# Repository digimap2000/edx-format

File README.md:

# EDX, the Electronics Design eXchange

EDX is an open, tool-neutral file format for printed circuit board design data. The design side states what the
board is and what it must achieve: outline, stack-up, packages, parts, nets, regions, pours, design-intent
relations, rules and explicit constraints. A layout engine decides how, and returns placement, copper and a report
in the same terms.

An EDX document is one JSON file (`*.edx.json`) with optional sections: `design`, `rules`, `constraints`, and the
engine's `layout` and `report`. Documents holding different sections, such as a design and a set of rules, merge into
one. Areas are written as SVG path data.

**Status:** pre-release. The specification, [`spec/edx.md`](spec/edx.md), is a working draft of version 1.0; nothing is stable yet.

## What lives here

| Folder | Contents |
| --- | --- |
| `spec/` | The specification, the normative definition of EDX |
| `schema/` | The JSON Schema (2020-12) for an EDX document, normative alongside the spec |
| `conformance/` | Language-neutral test cases and example documents |
| `crates/edx-format/` | Reference library in Rust: check, read, merge and write EDX documents |
| `crates/edx-cli/` | `edx`, the command-line checker and merger |
| `crates/edx-kicad/` | Converts KiCad 6+ boards to EDX (`edx from-kicad`), with no KiCad running |
| `bindings/python/` | The Python package `edx-format`, built on the Rust library |
| `bindings/js/` | The JavaScript package `edx-format`, the Rust library compiled to WebAssembly |
| `site/` | The GitHub Pages site that serves the schema at its `$id` |
| `tools/` | Scripts that check the suite against the schema and run it against any implementation |

## The reference library

The Rust crate `edx-format` checks a document in the four layers of the specification (parse, version and
extensions, schema, semantics), reads it into a typed model that keeps every `extensions` and `extras` member, merges
documents by record identity, and writes them back, plainly or in canonical form, with the section hashes a layout
engine records.

```rust
let checked = edx_format::check(&std::fs::read("board.edx.json")?);
for diagnostic in &checked.diagnostics {
    println!("{diagnostic}"); // error EDX-E2001: /design/parts/3/package: no package `SOT23`
}
if let Some(document) = checked.document.filter(|_| checked.is_ok()) {
    println!("{} parts", document.design.and_then(|d| d.parts).map_or(0, |p| p.len()));
}
```

The `edx` command does the same from a shell:

```sh
cargo install --path crates/edx-cli
edx check board.edx.json                 # exit status 1 when the document has errors
edx check --format json board.edx.json   # diagnostics as JSON, for other tools
edx merge design.edx.json rules.edx.json -o merged.edx.json
edx fmt board.edx.json                   # canonical form (section 13 of the spec)
edx hash board.edx.json                  # sha256 of the design, rules and constraints
edx constraints board.edx.json           # the constraints in force, derived and authored
edx explain EDX-E3005
edx from-kicad board.kicad_pcb -o board.edx.json   # a KiCad 6+ board as EDX
```

Converting from KiCad is one of the free utilities offered beside the specification; see
[`crates/edx-kicad`](crates/edx-kicad/README.md) for what goes where.

To depend on it from another Rust project before it is on crates.io:

```toml
edx-format = { git = "https://github.com/digimap2000/edx-format" }
```

## Python and JavaScript

Both packages wrap the same Rust core, so their results match it exactly, and both install the same `edx` command.
Documents are plain dictionaries or objects. See [`bindings/python`](bindings/python/README.md) and
[`bindings/js`](bindings/js/README.md).

```sh
pip install ./bindings/python                      # needs a Rust toolchain; builds with maturin
cd bindings/js && npm run build && npm test        # needs the wasm32 target and wasm-bindgen-cli
```

## Running the conformance suite

```sh
cargo test                                         # the reference library, including the whole suite
python tools/conformance.py target/debug/edx       # any implementation with the same command-line interface
python tools/conformance.py node bindings/js/bin/edx.cjs
```

## Licences

- Code: MIT OR Apache-2.0, at your option (`LICENSE-MIT`, `LICENSE-APACHE`).
- Specification text and schemas: Creative Commons Attribution 4.0 (`LICENSE-CC-BY-4.0`).
- Conformance fixtures: CC0 1.0 (`conformance/LICENSE-CC0`), so any project can copy them into its own tests.

## Contributing

Changes to the specification are proposed by pull request. Each change states what it adds, whether it is backwards
compatible within the current major version, and comes with conformance cases.

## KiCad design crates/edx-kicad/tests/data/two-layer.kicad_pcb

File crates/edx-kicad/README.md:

# edx-kicad

Converts a KiCad board (`.kicad_pcb`, KiCad 6 and later) to an EDX document, with no KiCad running. The project file
beside the board (`.kicad_pro`) supplies the net classes. It is one of the free utilities that come with the EDX
specification and libraries.

```sh
edx from-kicad board.kicad_pcb -o board.edx.json          # design, rules and the author's layout
edx from-kicad --no-layout --fixed locked board.kicad_pcb # the design and rules only
```

```rust
let board = std::fs::read_to_string("board.kicad_pcb")?;
let project = std::fs::read_to_string("board.kicad_pro").ok();
let converted = edx_kicad::convert(&board, project.as_deref(), &edx_kicad::Options::default())?;
std::fs::write("board.edx.json", edx_format::to_string(&converted.document))?;
for note in converted.notes {
    eprintln!("{note}"); // what was left out or approximated
}
```

## What goes where

| KiCad | EDX |
| --- | --- |
| Edge.Cuts lines, arcs, circles, rectangles, polygons and curves, on the board or in footprints | `design.board.outline`; closed loops inside others are cut-outs. A board with no closed loop has no outline, and a note says so |
| Copper layers `F.Cu`, `In1.Cu` … `B.Cu` | `stackup` layers `top`, `In1` … `bottom` |
| The board's physical stack-up | `copper_thickness`, `dielectric` (sublayers merged, permittivity averaged by thickness) and `mask` |
| An inner layer at least half covered by one net's zones, with no other net's tracks | a `plane` layer with that `plane_net` |
| A footprint | a package (pads and courtyard as seen from the top) and a part; footprints of the same geometry share a package |
| Pads: rect, circle, oval, roundrect | the same shapes |
| Pads: trapezoid, chamfered, custom | `polygon` (a chamfered pad's other corners are square; a custom pad is its anchor and filled primitives joined) |
| Courtyard (`F.CrtYd` or `B.CrtYd`, the part's own side) | `courtyard.top`; a footprint with none is converted without one (readers then take the nominal courtyard round its pads) |
| Net classes and their nets (`.kicad_pro`) | `rules.classes`; `Default` is `default` |
| Minimum track width, copper to edge, hole to hole | `TrackWidth.min`, `rules.board` |
| Copper zones | `design.pours`, ranked by KiCad's priority, then by the order they are written in |
| Keep-out zones and rule areas | `design.regions` |
| Where each footprint is, its tracks, arcs and vias | `layout` (unless `--no-layout`), with the hashes of the design and rules it was made from |

Each part is `fixed` where the author put it or `free` for a layout engine to place (`--fixed`):

- `edge` (the default): parts the author locked, mounting holes and fiducials, and parts whose courtyard comes within 1
  mm of the outline or crosses it, such as connectors;
- `locked`: only the parts the author locked;
- `all` or `none`.

A part on the bottom is turned half a turn more in EDX than in KiCad: EDX mirrors a package left to right, KiCad top to
bottom.

Left out: silkscreen and other graphics, text, footprints with no pads, filled zone copper, teardrops, nets that reach
no pad or that KiCad names `unconnected-(...)`, and copper on no net. KiCad 5 boards are refused: open and
save them in KiCad 6 or later first.

## Licence

MIT OR Apache-2.0. The boards in `tests/data` were written for these tests and are CC0, like the conformance fixtures.

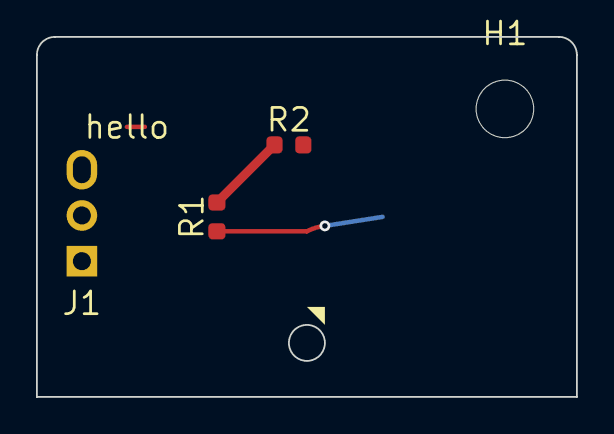
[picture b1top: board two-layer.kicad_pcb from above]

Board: 2 copper layers, 30.0 x 20.0 mm, 6 parts (1 on the bottom side), 3 nets.

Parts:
C1: 100n; C_0603_1608Metric
G1: Logo
H1: M3; MountingHole_3.2mm_M3
J1: Conn; PinHeader_1x03_P2.54mm_Vertical
R1: 10k; R_0603_1608Metric
R2: 1k; R_0603_1608Metric

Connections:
+5V: J1.1, R1.2, R2.1
GND: C1.2, J1.2, R2.2
SIG: C1.1, R1.1
